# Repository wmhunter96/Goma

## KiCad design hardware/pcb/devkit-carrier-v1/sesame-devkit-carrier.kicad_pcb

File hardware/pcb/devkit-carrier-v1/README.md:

# Sesame DevKit Carrier v1

Plug-in carrier board for a **30-pin ESP32 DevKit (DOIT DevKit V1 style, 1.0" / 25.4 mm between pin rows)**.
Replaces hand wiring: 3S battery in (solder pads for a pigtail), onboard 5V/5A regulator, 8 servo headers, OLED header, battery voltage sense, spare I/O.

- Board: **69 × 42 mm**, 2 layers, 1.6 mm, all through-hole
- The DevKit's **antenna end hangs off the left edge** of the board, so the whole antenna is in open air (best Wi-Fi range). USB points inward, so **flash the DevKit before plugging it into the carrier** (it pops out of the sockets if you ever need to reflash)
- Pin map matches the firmware's "Distro Board V1 / DevKit" settings, so no firmware pin changes are needed
- Generated by `build_board.py` (run with KiCad 10's bundled python). Edit the script, not the `.kicad_pcb`, then re-run it.
- `gen_schematic.py` then generates the matching schematic (`sesame-devkit-carrier.kicad_sch`, PDF in `preview/schematic.pdf`) from the board, with named, typed pins for the DevKit rows and the Pololu module (`Sesame.kicad_sym`). Footprints live in the project library `Sesame.pretty`; `sym-lib-table`/`fp-lib-table` make the project self-contained.
- Independent review with kicad-happy: see `REVIEW.md` (ready to order).
- Checks, all clean: ERC 0 errors / 0 warnings; DRC with schematic parity 0 violations / 0 footprint errors; `audit.py` (an independent electrical check: netlist vs spec, firmware pin match, current capacity, ground fill, polarity, labels, screw-head keep-outs) passes — last result in `audit.txt`.

Rebuild everything after a change:

```
python build_board.py && python gen_schematic.py          (KiCad 10's bundled python)
kicad-cli sch erc --severity-all sesame-devkit-carrier.kicad_sch
kicad-cli pcb drc --schematic-parity --severity-all --refill-zones sesame-devkit-carrier.kicad_pcb
python audit.py
python short_check.py        (plain python, no KiCad: short-risk margins)
```
- `sesame-devkit-carrier.step` is the 3D model for designing the body around the board.

## Layout

```
          L1          L2 L4    L3 R3 R4 R2 R1
        ┌───────────────────────────────────────────────────────────────────┐
        │ - ▪          ▪ ▪     ▪ ▪ ▪ ▪ ▪   -        ◯     ┌──────────────┐  │
        │ + ▪──────────▪─▪─────▪─▪─▪─▪─▪   +  (servo 5V)  │ Pololu       │ ◯│
        │ S ▪          ▪ ▪     ▪ ▪ ▪ ▪ ▪   S              │ D24V50F5     │  │
 ┌──────┼─────────────────────────────────────────┐       │EN VIN G G OUT│  │
 │ ANT  │ ESP32 DevKit (two 1×15 sockets)   USB ->│       └──────────────┘  │
 │(over-│        battery divider underneath   ◯   │      (C1)     BATT 3S   │
 │hangs)│                                         │                BAT+ ■   │
 └──────┼─────────────────────────────────────────┘                BAT- ●   │
        │ C D V G   32 33 25 26 27 14   13 G 5V            SW ● ●        ◯  │
        │ OLED      spare I/O                                               │
        └───────────────────────────────────────────────────────────────────┘
```

The ESP32's antenna sits past the carrier's left edge with nothing under it, per Espressif's antenna-placement guidance. In the body design, keep metal (screws, battery, wires) away from that overhanging end of the DevKit.

## Ordering (PCBWay)

Upload `sesame-devkit-carrier-gerbers.zip`. Settings: 2 layers, 69 × 42 mm, 1.6 mm FR-4, 1 oz copper, HASL (lead-free) finish, any mask colour.

## Parts

| Ref | Part | Qty | Notes |
|---|---|---|---|
| J1, J2 | 1×15 female header, 2.54 mm, 8.5 mm tall | 2 | DevKit plugs in here |
| U1 | Pololu D24V50F5 (5V 5A step-down, #2851) | 1 | Solder straight into the board on its included 5-pin header. EN is left unconnected (pulled up on the module) |
| J6 | Battery pigtail pads (3.9 mm pads, 2.15 mm holes) | — | Solder a 16–18 AWG XT30 pigtail (female, to mate with the battery). Square pad = BAT+. Hot-glue or zip-tie the wires so they can't flex at the joint |
| SW1 | Wire pads for the power switch | — | 18 AWG to your rocker switch. No switch? Bridge the two pads with wire |
| S1–S8 | 1×3 male header, 2.54 mm | 8 | Servo plugs. Can be cut from 40-pin strips |
| J3 | 1×4 male header | 1 | OLED: C D V G = SCL, SDA, 3V3, GND |
| J4, J5 | 1×6 + 1×3 male header | 1 each | Spare I/O (optional) |
| C1 | 470 µF 16 V electrolytic, 8 mm dia, 3.5 mm pitch, ≤ 12 mm tall (e.g. Panasonic EEU-FR1C471) | 1 | 5V bulk cap. Mind polarity (+ marked) |
| C3 | 47 µF 35 V electrolytic, 5 mm dia, 2.0 or 2.5 mm pitch, ≤ 11 mm tall | 1 | Regulator input: damps the voltage spike when the battery/switch connects. Must be 35 V or higher. Mind polarity (+ marked). Footprint is 2.5 mm pitch with narrowed pads for a 1.3 mm gap (it sits across the battery); a 2.0 mm-pitch cap's leads bend out slightly to fit |
| R1 | 100 kΩ ¼ W (1% preferred) | 1 | Battery divider top |
| R2 | 22 kΩ ¼ W (1% preferred) | 1 | Battery divider bottom |
| C2 | 100 nF ceramic, 5 mm pitch | 1 | Sense filter |
| H1–H5 | M2.5 mounting holes (socket-head cap screws, 4.5 mm head) | 5 | Corners, top-middle, and two under the DevKit (fit those before plugging the DevKit in). 3 mm copper keep-out: only ground fill under a screw head |
| HP1, HP2 | M2 holes under the Pololu's own mounting holes (M2 socket head, 3.8 mm) | 2 | One M2 screw through the module, a 3D-printed standoff (≈2.5 mm tall, ≤ 4 mm OD at HP1) and the carrier. 2.4 mm copper keep-out |

Solder R1, R2 and C2 **before** the DevKit sockets; they sit underneath the DevKit and must stay under ~7 mm tall.

## Pin map

| Function | DevKit pin | Board |
|---|---|---|
| Servo L1 / L2 / L3 / L4 | D23 / D19 / TX2 (17) / D18 | S headers, labelled |
| Servo R1 / R2 / R3 / R4 | D15 / D2 / RX2 (16) / D4 | S headers, labelled |
| OLED SDA / SCL | D21 / D22 | J3 |
| Battery sense | D34 (GPIO34, ADC1) | via 100k/22k divider, after the switch |
| Spare I/O | D32 D33 D25 D26 D27 D14 D13, GND, 5V | J4, J5 (each pin directly below its DevKit pin) |
| 5V in | VIN | from U1 |

Servo headers are **S + −** from the DevKit outward: orange toward the DevKit, brown on the outer (−) pin, nearest the top edge.

## Before you power it

1. **Check your DevKit's printed labels** against the silkscreen: antenna hanging off the left edge, USB pointing right, D23 at the antenna end of the row nearest the servo headers. Also check that the antenna (the zig-zag copper end of the module) starts at least ~2.5 mm past pin 1, so it clears the board edge.
2. **Pigtail polarity:** red to the square **BAT+** pad, black to **BAT−**. Plug the pigtail into the battery and check with a multimeter before soldering. The Pololu module has reverse-voltage protection, but check anyway.
3. With nothing plugged in, use continuity mode: 5V to GND, and battery + to GND, must **not** beep.
4. First power-up with the DevKit only, no servos. Measure 5V at the servo + pins before plugging servos in.

## If something beeps (finding a short)

On this board a short is almost certainly a solder bridge or a backwards part. It is a 2-layer board, so there are no buried layers to fail, and PCBWay electrically tests bare boards. Bare pads are at least 0.84 mm apart, ground fill stays 0.5 mm back from everything, and `short_check.py` enforces those margins.

Work with everything unplugged: no battery, no DevKit, no servos.

| Beeps between | Where to look, most likely first |
|---|---|
| 5V and GND | Servo headers: the **+** and **−** pins are neighbours (8 headers, 16 joints). J5: **G** and **5V** are neighbours. U1: pin 4 (GND) beside pin 5 (OUT). C1 in backwards. |
| Battery + and GND | U1: pin 2 (VIN) beside pin 3 (GND). C3 in backwards. SW1 or J6 wire strands touching the next pad. |
| 3V3 and GND | J3: **V** and **G** are neighbours. DevKit socket J2: 3V3 is next to GND at the USB end. |
| Two signals, or a signal and 5V/GND | DevKit sockets J1/J2 (15 pins each) and J4. Check every adjacent pair. |

How to find it:

1. **Look first.** Put a phone flashlight behind the board and look along each row of pins with a magnifier or phone macro. Bridges show up as a shiny blob joining two pads.
2. **Halve the search.** If continuity mode can't tell you where, cut the board in half electrically. Unplug anything that unplugs, then check whether the short is on the servo side, the OLED/I-O side or the regulator side. A loose servo-header joint only takes a few seconds to reflow.
3. **Fix a bridge.** Add flux, then drag a clean, tinned iron tip between the two pins. If that doesn't clear it, use solder wick.
4. **Backwards electrolytic** (C1, C3): the stripe on the can marks **−**. The square pad, marked **+** on the silkscreen, takes the long leg. Replace it if it was ever powered backwards.
5. **Still shorted with nothing obvious?** Use the multimeter's resistance mode. The reading drops as you move the probe toward the short, so follow the lowest reading.

## Battery reading in firmware

`V_battery = V_GPIO34 × (100k + 22k) / 22k = V_GPIO34 × 5.545` (12.6 V full charge reads as 2.27 V, inside the ESP32 ADC's accurate 0.15–2.45 V range)

```cpp
float batteryVolts() {
  return analogReadMilliVolts(34) * 5.5455f / 1000.0f;   // 12.6 V full, ~10.5 V time to charge (3S)
}
```

## Verified against official documentation

| Item | Source | What was checked |
|---|---|---|
| ESP32 DevKit pinout | AITRIP listing photo (B08D5ZD528) | Pin order both rows, VIN/3V3 at USB end, 25.4 mm row spacing (measured), antenna starts ~5 mm past pin 1 (measured) |
| ESP32 pins | Espressif ESP32 datasheet v5.3 | GPIO34 = ADC1_CH6, input-only; strapping pins GPIO0/2/5/12/15 and their boot levels; ADC 12 dB range 150–2450 mV; 100 nF on the ADC input as in the datasheet test setup |
| Pololu D24V50F5 | pololu.com/product/2851 + dimension drawing 0J1436 | 6–38 V in, 5 V ±4 % out, reverse protection, EN pulled up; pin row 1.27 mm from edge, OUT 1.91 mm from right edge, 2.54 mm pitch, 1.02 mm holes |
| Hot-plug spikes | Pololu app note 0J16 | Spikes can exceed 3× the supply, worse with switch bounce; fix is an electrolytic across the input → C3 |
| C1 | Panasonic EEU-FR1C471 (distributor listings) | 8 mm dia, 3.5 mm lead spacing, 16 V |
| Fabrication limits | pcbway.com/capabilities | Tracks ≥ 0.40 mm (min 0.10): signals 0.5 mm, necked to 0.4 mm only between socket pins; power 1.5–2.0 mm, vias 0.4/0.8 mm, annular ring ≥ 0.35 mm (min 0.15), silkscreen text ≥ 0.8 mm and lines ≥ 0.15 mm |

KiCad DRC is clean (0 violations). Headers that deliberately sit side by side on the 2.54 mm grid are allowed in `sesame-devkit-carrier.kicad_dru`; `audit.py` checks their real spacing instead.

## Notes

- Antenna: overhangs the board edge entirely, to keep Wi-Fi range.
- The DevKit's own micro-USB is used for flashing (with the DevKit out of the carrier); there's deliberately no second USB-serial chip on the carrier.
- `build_board.py` is the source of truth for every connection; the schematic is generated from the board by `gen_schematic.py`.
- Board art: Sesame's own `cute` face `( 〃>ᴗ<〃 )`, read pixel-for-pixel from `firmware/face-bitmaps.h` at build time. Big on the back, half-resolution on the front (kept above the 0.15 mm silkscreen minimum).

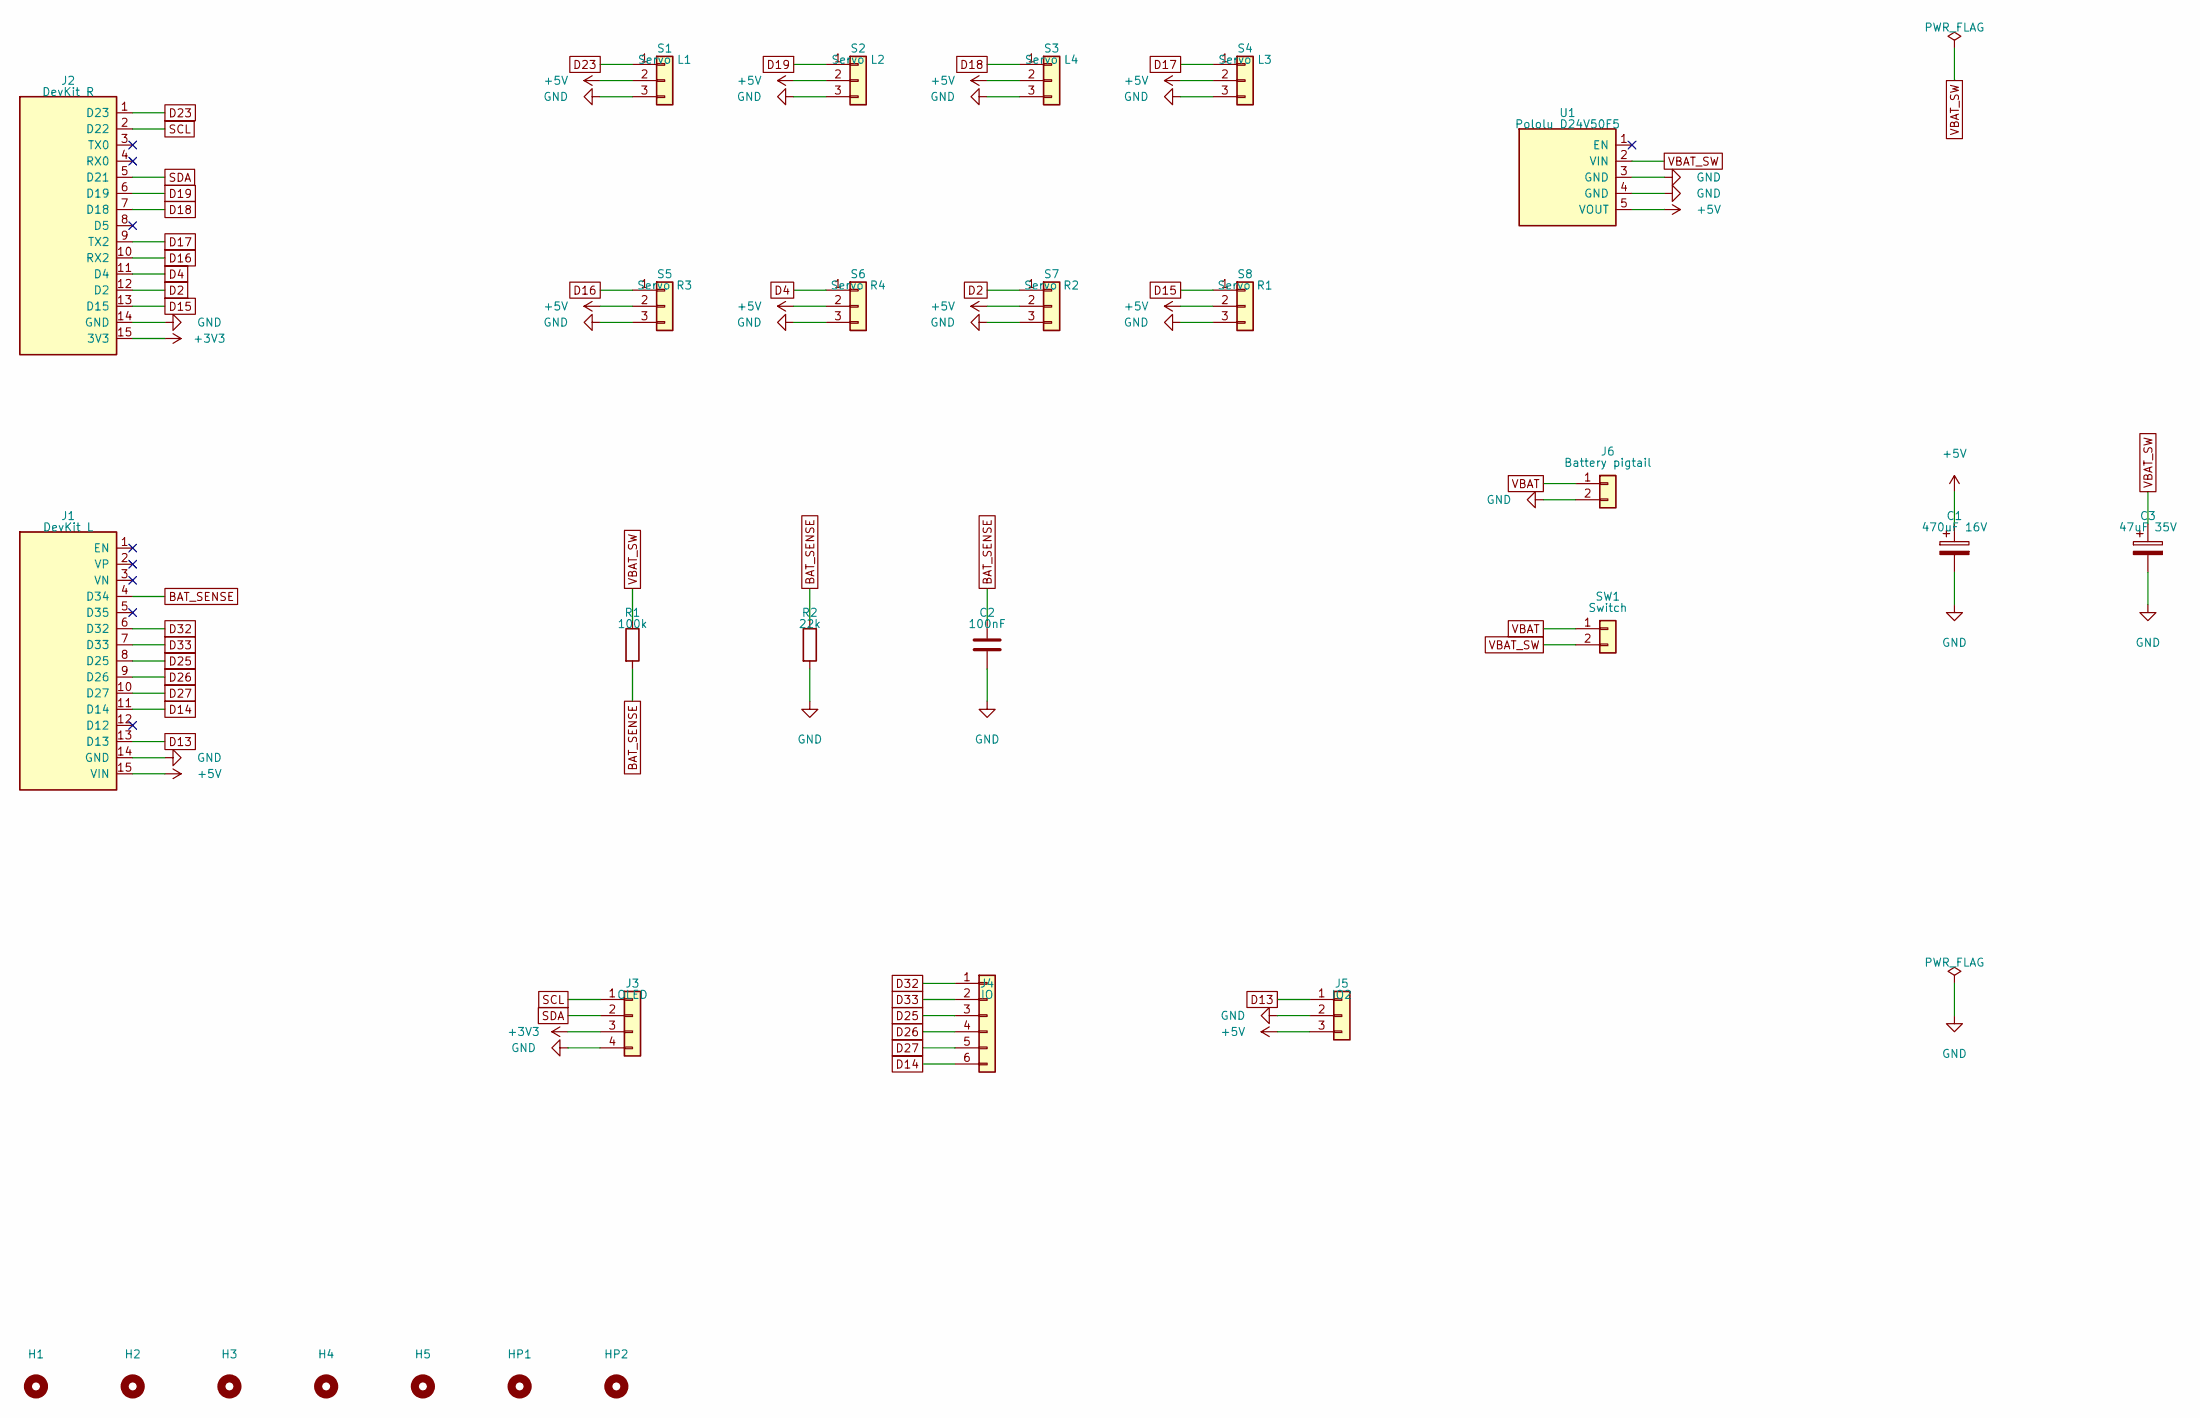
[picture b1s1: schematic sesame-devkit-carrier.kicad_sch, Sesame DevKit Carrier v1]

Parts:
C1: 470uF 16V; CP_Radial_D8.0mm_P3.50mm
C2: 100nF; C_Disc_D5.0mm_W2.5mm_P5.00mm
C3: 47uF 35V; CP_Radial_D5.0mm_P2.50mm
H1, H2, H3, H4, H5: MountingHole_2.7mm_M2.5
HP1, HP2: MountingHole_2.2mm_M2
J1: DevKit L; PinSocket_1x15_P2.54mm_Vertical_GroupSilk
J2: DevKit R; PinSocket_1x15_P2.54mm_Vertical_GroupSilk
J3: OLED; PinHeader_1x04_P2.54mm_Vertical_GroupSilk
J4: IO; PinHeader_1x06_P2.54mm_Vertical_GroupSilk
J5: IO2; PinHeader_1x03_P2.54mm_Vertical_GroupSilk
J6: Battery pigtail; SolderWire-1.5sqmm_1x02_P7.8mm_D1.7mm_OD3.9mm
R1: 100k; R_Axial_DIN0207_L6.3mm_D2.5mm_P10.16mm_Horizontal
R2: 22k; R_Axial_DIN0207_L6.3mm_D2.5mm_P10.16mm_Horizontal
S1: Servo L1; PinHeader_1x03_P2.54mm_Vertical_GroupSilk
S2: Servo L2; PinHeader_1x03_P2.54mm_Vertical_GroupSilk
S3: Servo L4; PinHeader_1x03_P2.54mm_Vertical_GroupSilk
S4: Servo L3; PinHeader_1x03_P2.54mm_Vertical_GroupSilk
S5: Servo R3; PinHeader_1x03_P2.54mm_Vertical_GroupSilk
S6: Servo R4; PinHeader_1x03_P2.54mm_Vertical_GroupSilk
S7: Servo R2; PinHeader_1x03_P2.54mm_Vertical_GroupSilk
S8: Servo R1; PinHeader_1x03_P2.54mm_Vertical_GroupSilk
SW1: Switch; SolderWire-1sqmm_1x02_P5.4mm_D1.4mm_OD2.7mm
U1: Pololu D24V50F5; PinHeader_1x05_P2.54mm_Vertical_GroupSilk

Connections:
+3V3: J2.15 (3V3), J3.3
+5V: C1.1, J1.15 (VIN), J5.3, S1.2, S2.2, S3.2, S4.2, S5.2, S6.2, S7.2, S8.2, U1.5 (VOUT)
BAT_SENSE: C2.1, J1.4 (D34), R1.2, R2.1
D2: J2.12 (D2), S7.1
D4: J2.11 (D4), S6.1
D13: J1.13 (D13), J5.1
D14: J1.11 (D14), J4.6
D15: J2.13 (D15), S8.1
D16: J2.10 (RX2), S5.1
D17: J2.9 (TX2), S4.1
D18: J2.7 (D18), S3.1
D19: J2.6 (D19), S2.1
D23: J2.1 (D23), S1.1
D25: J1.8 (D25), J4.3
D26: J1.9 (D26), J4.4
D27: J1.10 (D27), J4.5
D32: J1.6 (D32), J4.1
D33: J1.7 (D33), J4.2
GND: C1.2, C2.2, C3.2, J1.14 (GND), J2.14 (GND), J3.4, J5.2, J6.2, R2.2, S1.3, S2.3, S3.3, S4.3, S5.3, S6.3, S7.3, S8.3, U1.3 (GND), U1.4 (GND)
SCL: J2.2 (D22), J3.1
SDA: J2.5 (D21), J3.2
VBAT: J6.1, SW1.1
VBAT_SW: C3.1, R1.1, SW1.2, U1.2 (VIN)

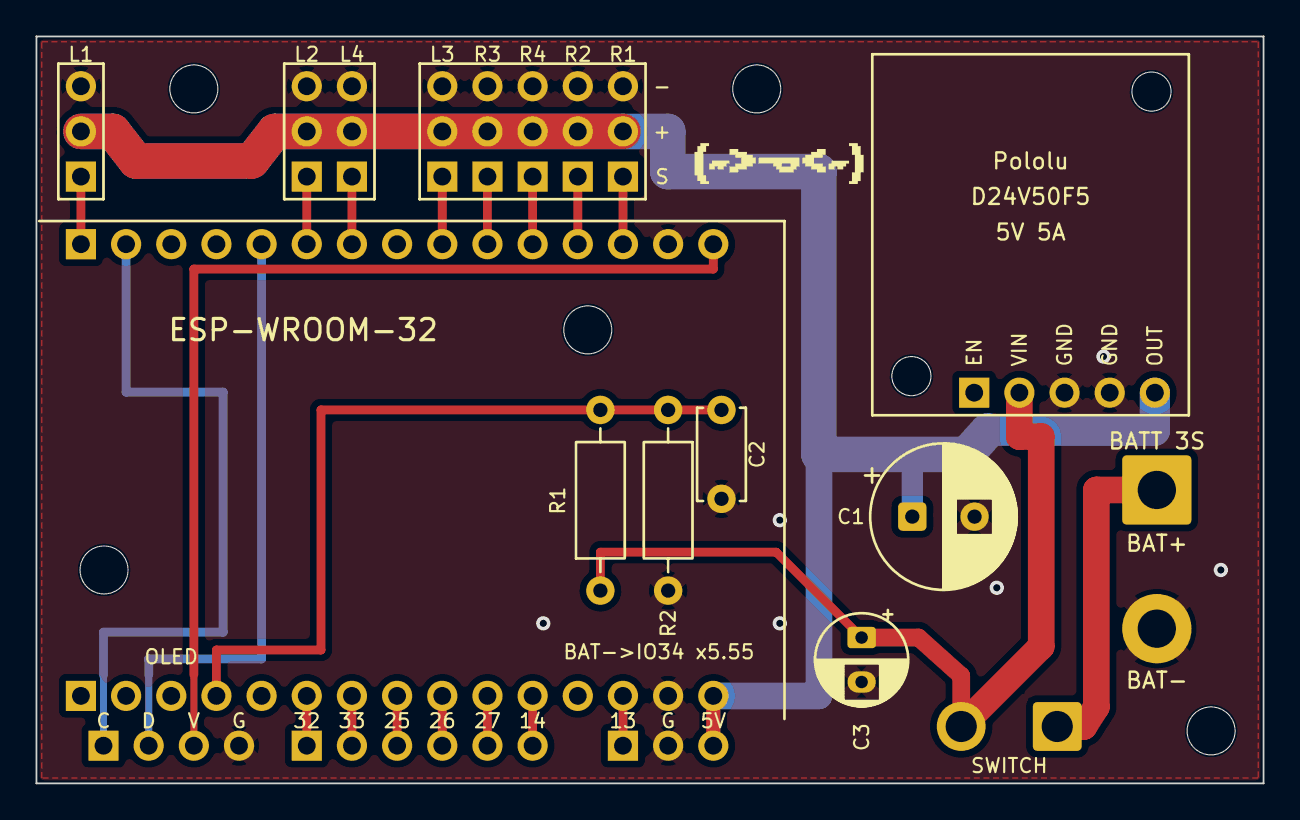
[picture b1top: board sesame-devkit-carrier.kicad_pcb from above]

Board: 2 copper layers, 69.0 x 42.0 mm, 28 parts (0 on the bottom side), 23 nets.
